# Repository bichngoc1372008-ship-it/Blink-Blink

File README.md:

# Blink-Blink
A Sakura board with 10 LEDs flashing in sequence using NE555P to control the pattern. 
Schematic            |  PCB         |   3D
:-------------------------:|:-------------------------:|:-------------------------:|
   |    |

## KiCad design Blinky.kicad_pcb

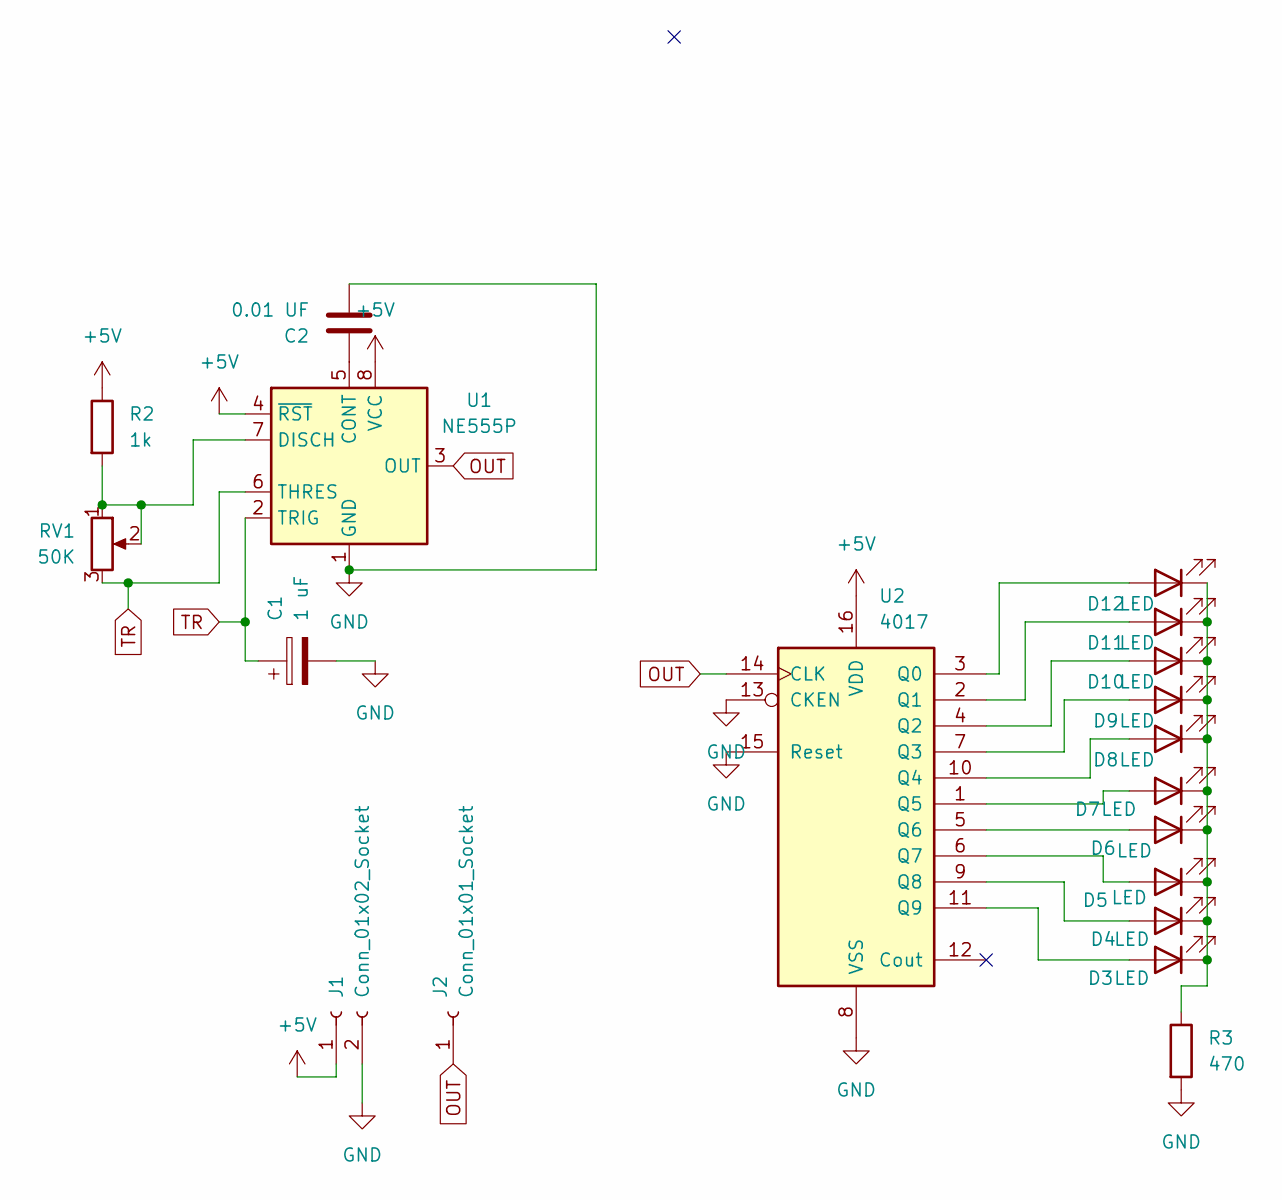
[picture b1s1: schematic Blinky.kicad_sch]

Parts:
C1: 1 uF; CP_Radial_D5.0mm_P2.00mm
C2: 0.01 UF; C_Disc_D7.5mm_W2.5mm_P5.00mm
D3, D4, D5, D6, D7, D8, D9, D10, D11, D12: LED; LED_D3.0mm
J1: Conn_01x02_Socket; PinHeader_1x02_P2.54mm_Vertical
J2: Conn_01x01_Socket; PinHeader_1x01_P2.54mm_Vertical
R2: 1k; R_Axial_DIN0207_L6.3mm_D2.5mm_P7.62mm_Horizontal
R3: 470; R_Axial_DIN0207_L6.3mm_D2.5mm_P7.62mm_Horizontal
RV1: 50K; Potentiometer_Vishay_T93YA_Vertical
U1: NE555P; DIP-8_W7.62mm
U2: 4017; N16

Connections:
+5V: J1.1, R2.1, U1.4 (~RST), U1.8 (VCC), U2.16 (VDD)
GND: C1.2, C2.2, J1.2, R3.2, U1.1 (GND), U2.8 (VSS), U2.13 (CKEN), U2.15 (Reset)
unnamed: D3.2 (A), U2.11 (Q9)
unnamed: D4.2 (A), U2.9 (Q8)
unnamed: D5.2 (A), U2.6 (Q7)
unnamed: D6.2 (A), U2.5 (Q6)
unnamed: D7.2 (A), U2.1 (Q5)
unnamed: D8.2 (A), U2.10 (Q4)
unnamed: D9.2 (A), U2.7 (Q3)
unnamed: D10.2 (A), U2.4 (Q2)
unnamed: D3.1 (K), D4.1 (K), D5.1 (K), D6.1 (K), D7.1 (K), D8.1 (K), D9.1 (K), D10.1 (K), D11.1 (K), D12.1 (K), R3.1
unnamed: D11.2 (A), U2.2 (Q1)
unnamed: D12.2 (A), U2.3 (Q0)
unnamed: C2.1, U1.5 (CONT)
unnamed: R2.2, RV1.1, RV1.2, U1.7 (DISCH)
OUT: J2.1, U1.3 (OUT), U2.14 (CLK)
TR: C1.1, RV1.3, U1.2 (TRIG), U1.6 (THRES)

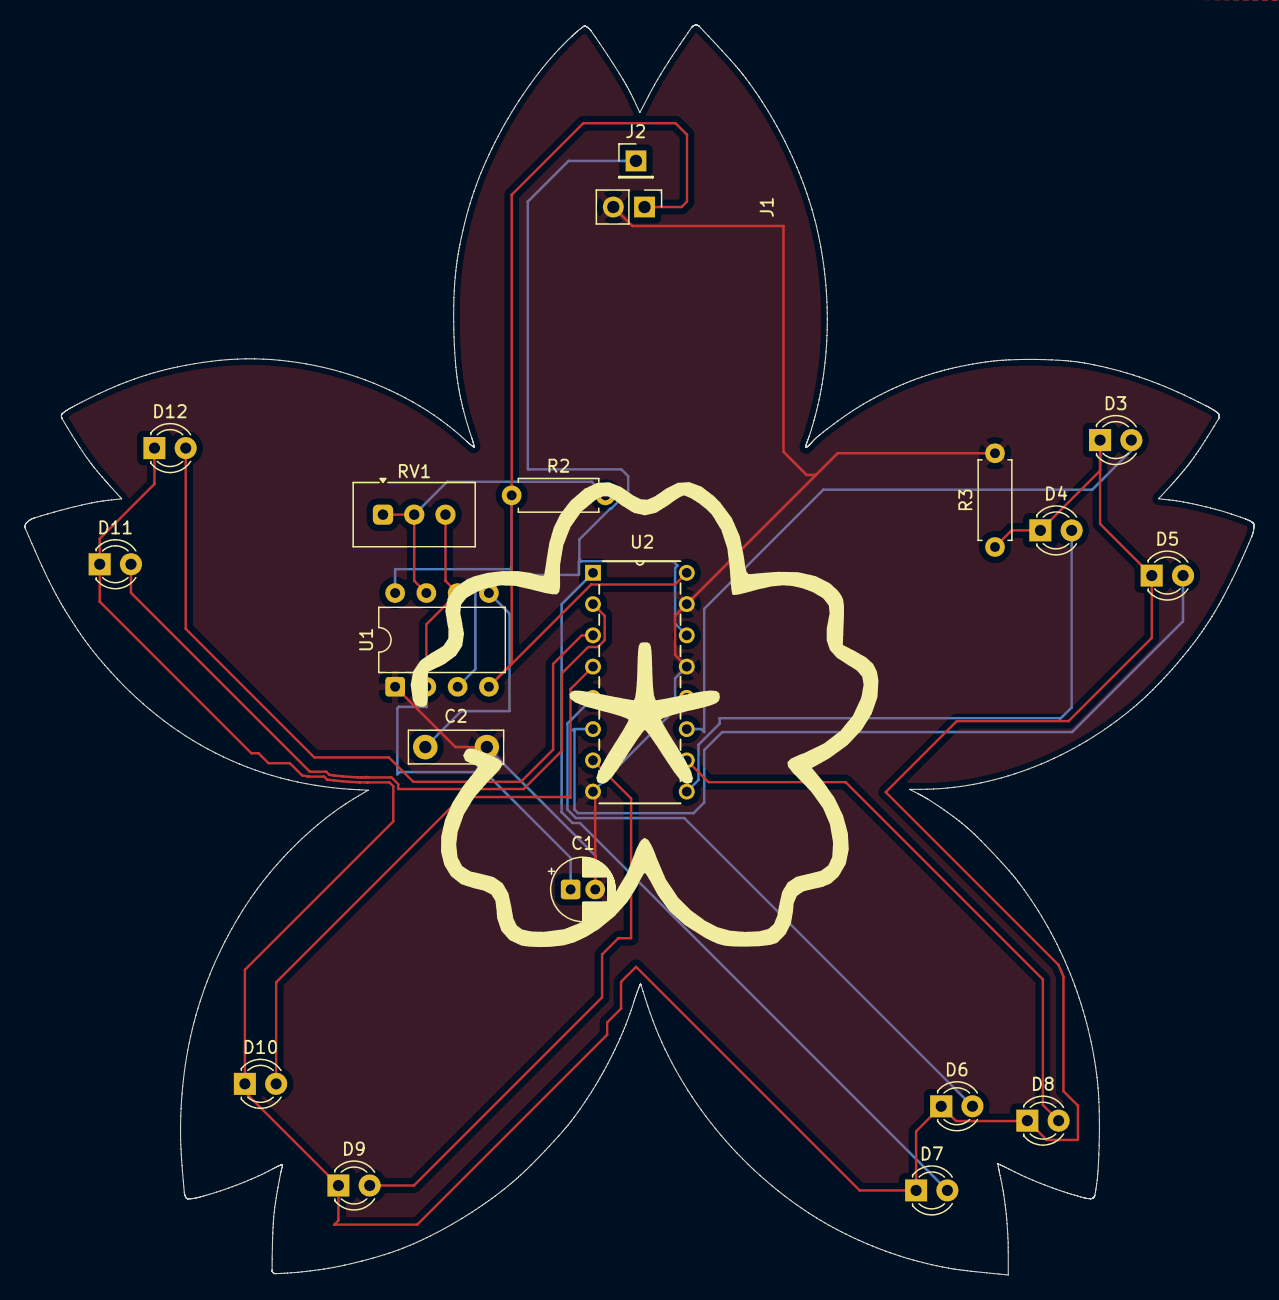
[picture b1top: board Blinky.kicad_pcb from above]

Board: 2 copper layers, 99.9 x 101.6 mm, 19 parts (0 on the bottom side), 17 nets.

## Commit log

2026-03-01 Picture
